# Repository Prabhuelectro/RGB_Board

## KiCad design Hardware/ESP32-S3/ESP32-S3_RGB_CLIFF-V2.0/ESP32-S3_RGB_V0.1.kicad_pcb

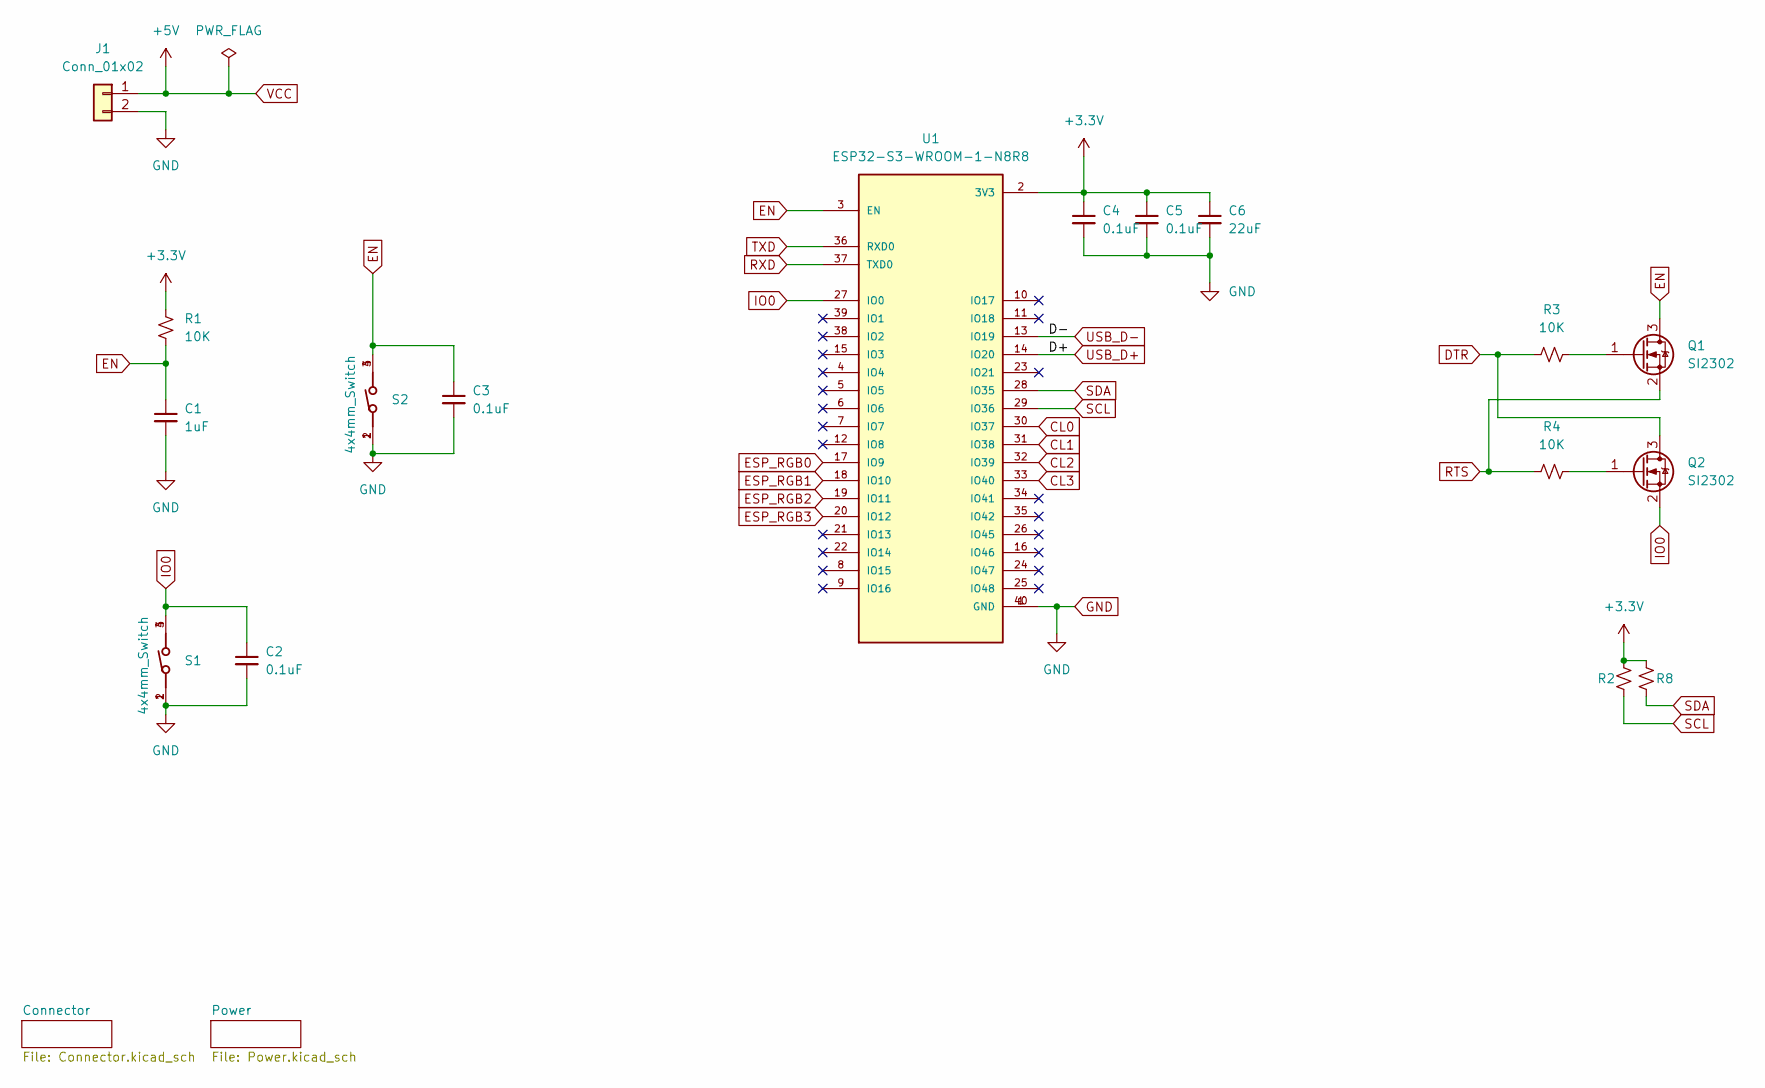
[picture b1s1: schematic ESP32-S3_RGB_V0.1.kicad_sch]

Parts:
C1: 1uF; C_0603_1608Metric
C2, C3, C4, C5: 0.1uF; C_0603_1608Metric
C6: 22uF; C_0603_1608Metric
J1: Conn_01x02; JST_VH_B2P-VH-B_1x02_P3.96mm_Vertical
Q1, Q2: SI2302; SOT-23
R1, R2, R3, R4, R8: 10K; R_0603_1608Metric
S1, S2: 4x4mm_Switch; 430181038816
U1: ESP32-S3-WROOM-1-N8R8; ESP32S3WROOM1N8R8

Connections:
+3.3V: C4.1, C5.1, C6.1, R1.1, R2.1, R8.1, U1.2 (3V3); also elsewhere on the board
CL0: U1.30 (IO37); also elsewhere on the board
CL1: U1.31 (IO38); also elsewhere on the board
CL2: U1.32 (IO39); also elsewhere on the board
CL3: U1.33 (IO40); also elsewhere on the board
DTR: Q2.3 (D), R3.2; also elsewhere on the board
EN: C1.1, C3.1, Q1.3 (D), R1.2, S2.3, S2.4, U1.3 (EN)
ESP_RGB0: U1.17 (IO9); also elsewhere on the board
ESP_RGB1: U1.18 (IO10); also elsewhere on the board
ESP_RGB2: U1.19 (IO11); also elsewhere on the board
ESP_RGB3: U1.20 (IO12); also elsewhere on the board
GND: C1.2, C2.2, C3.2, C4.2, C5.2, C6.2, J1.2, S1.1, S1.2, S2.1, S2.2, U1.1 (GND), U1.40 (GND); also elsewhere on the board
IO0: C2.1, Q2.2 (S), S1.3, S1.4, U1.27 (IO0)
unnamed: Q1.1 (G), R3.1
unnamed: Q2.1 (G), R4.1
RTS: Q1.2 (S), R4.2; also elsewhere on the board
RXD: U1.37 (TXD0); also elsewhere on the board
SCL: R2.2, U1.29 (IO36); also elsewhere on the board
SDA: R8.2, U1.28 (IO35); also elsewhere on the board
TXD: U1.36 (RXD0); also elsewhere on the board
USB_D+: U1.14 (IO20); also elsewhere on the board
USB_D-: U1.13 (IO19); also elsewhere on the board
VCC: J1.1; also elsewhere on the board

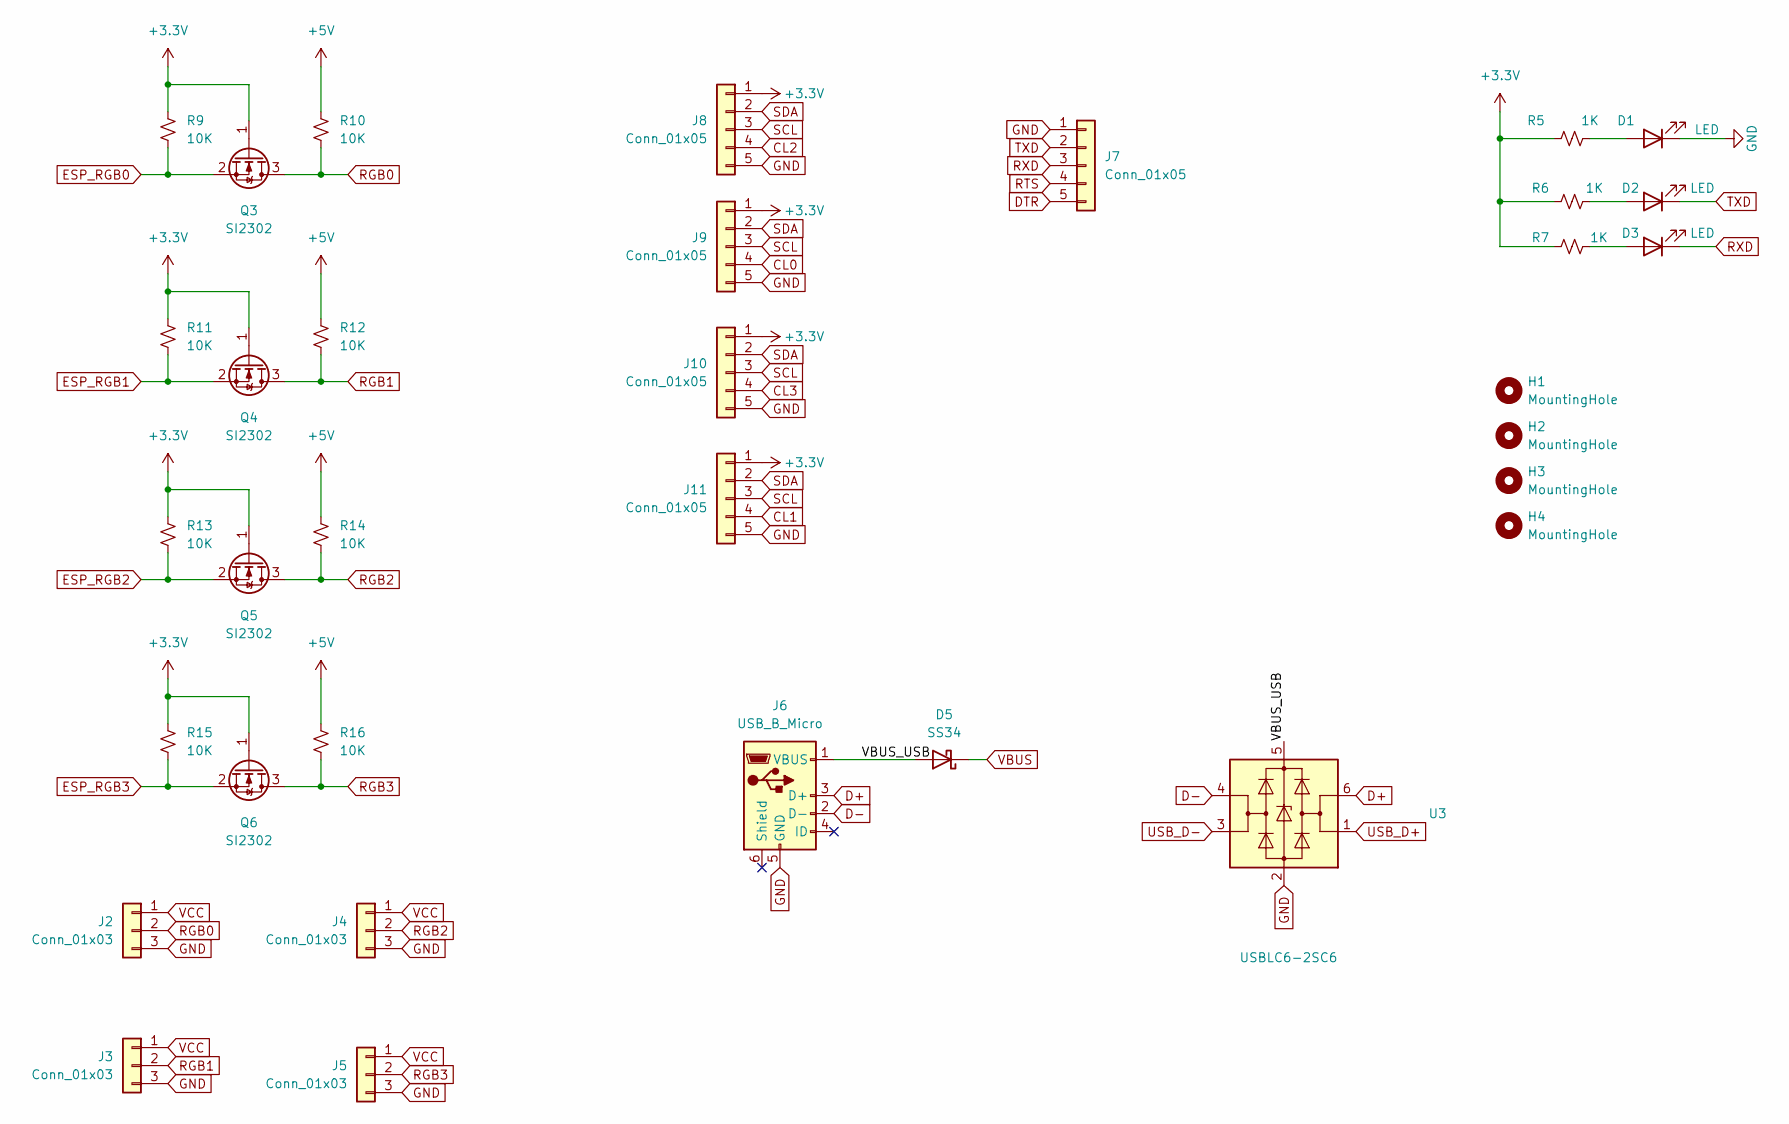
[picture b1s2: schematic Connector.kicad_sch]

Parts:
D1, D2, D3: LED; LED_0603_1608Metric
D5: SS34; D_SMA
H1, H2, H3, H4: MountingHole; MountingHole_3.2mm_M3
J2, J3, J4, J5: Conn_01x03; JST_PH_B3B-PH-K_1x03_P2.00mm_Vertical
J6: USB_B_Micro; USB_Micro-B_Wuerth_614105150721_Vertical
J7: Conn_01x05; PinHeader_1x05_P2.54mm_Vertical
J8, J9, J10, J11: Conn_01x05; JST_PH_B5B-PH-K_1x05_P2.00mm_Vertical
Q3, Q4, Q5, Q6: SI2302; SOT-23
R5, R6, R7: 1K; R_0603_1608Metric
R9, R10, R11, R12, R13, R14, R15, R16: 10K; R_0603_1608Metric
U3: USBLC6-2SC6; SOT-23-6

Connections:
+3.3V: J8.1, J9.1, J10.1, J11.1, Q3.1 (G), Q4.1 (G), Q5.1 (G), Q6.1 (G), R5.1, R6.1, R7.1, R9.1, R11.1, R13.1, R15.1; also elsewhere on the board
/Connector/VBUS_USB: D5.2 (A), J6.1 (VBUS), U3.5 (VBUS)
CL0: J9.4; also elsewhere on the board
CL1: J11.4; also elsewhere on the board
CL2: J8.4; also elsewhere on the board
CL3: J10.4; also elsewhere on the board
D+: J6.3 (D+), U3.6 (I/O1)
D-: J6.2 (D-), U3.4 (I/O2)
DTR: J7.5; also elsewhere on the board
ESP_RGB0: Q3.2 (S), R9.2; also elsewhere on the board
ESP_RGB1: Q4.2 (S), R11.2; also elsewhere on the board
ESP_RGB2: Q5.2 (S), R13.2; also elsewhere on the board
ESP_RGB3: Q6.2 (S), R15.2; also elsewhere on the board
GND: D1.1 (K), J2.3, J3.3, J4.3, J5.3, J6.5 (GND), J7.1, J8.5, J9.5, J10.5, J11.5, U3.2 (GND); also elsewhere on the board
unnamed: D1.2 (A), R5.2
unnamed: D2.2 (A), R6.2
unnamed: D3.2 (A), R7.2
RGB0: J2.2, Q3.3 (D), R10.2
RGB1: J3.2, Q4.3 (D), R12.2
RGB2: J4.2, Q5.3 (D), R14.2
RGB3: J5.2, Q6.3 (D), R16.2
RTS: J7.4; also elsewhere on the board
RXD: D3.1 (K), J7.3; also elsewhere on the board
SCL: J8.3, J9.3, J10.3, J11.3; also elsewhere on the board
SDA: J8.2, J9.2, J10.2, J11.2; also elsewhere on the board
TXD: D2.1 (K), J7.2; also elsewhere on the board
USB_D+: U3.1 (I/O1); also elsewhere on the board
USB_D-: U3.3 (I/O2); also elsewhere on the board
VBUS: D5.1 (K); also elsewhere on the board
VCC: J2.1, J3.1, J4.1, J5.1, R10.1, R12.1, R14.1, R16.1; also elsewhere on the board

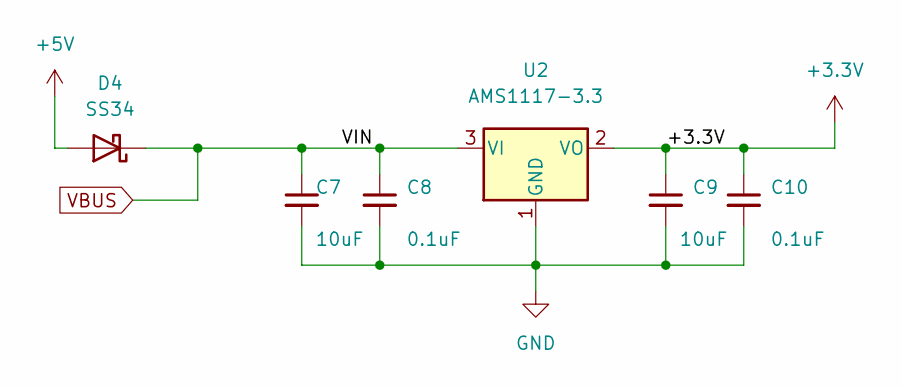
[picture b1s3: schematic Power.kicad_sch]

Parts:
C7, C9: 10uF; C_0603_1608Metric
C8, C10: 0.1uF; C_0603_1608Metric
D4: SS34; D_SMA
U2: AMS1117-3.3; SOT-223-3_TabPin2

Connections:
+3.3V: C9.1, C10.1, U2.2 (VO); also elsewhere on the board
GND: C7.2, C8.2, C9.2, C10.2, U2.1 (GND); also elsewhere on the board
VBUS: C7.1, C8.1, D4.1 (K), U2.3 (VI); also elsewhere on the board
VCC: D4.2 (A); also elsewhere on the board

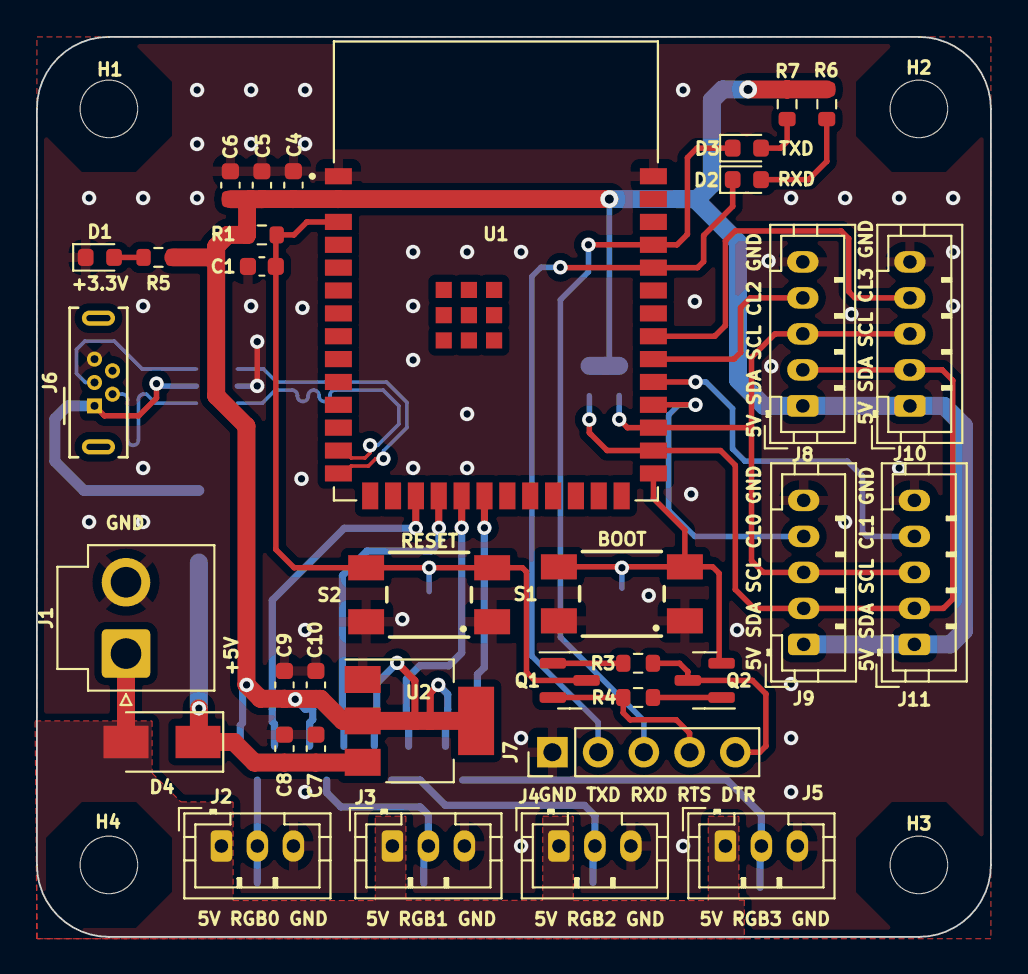
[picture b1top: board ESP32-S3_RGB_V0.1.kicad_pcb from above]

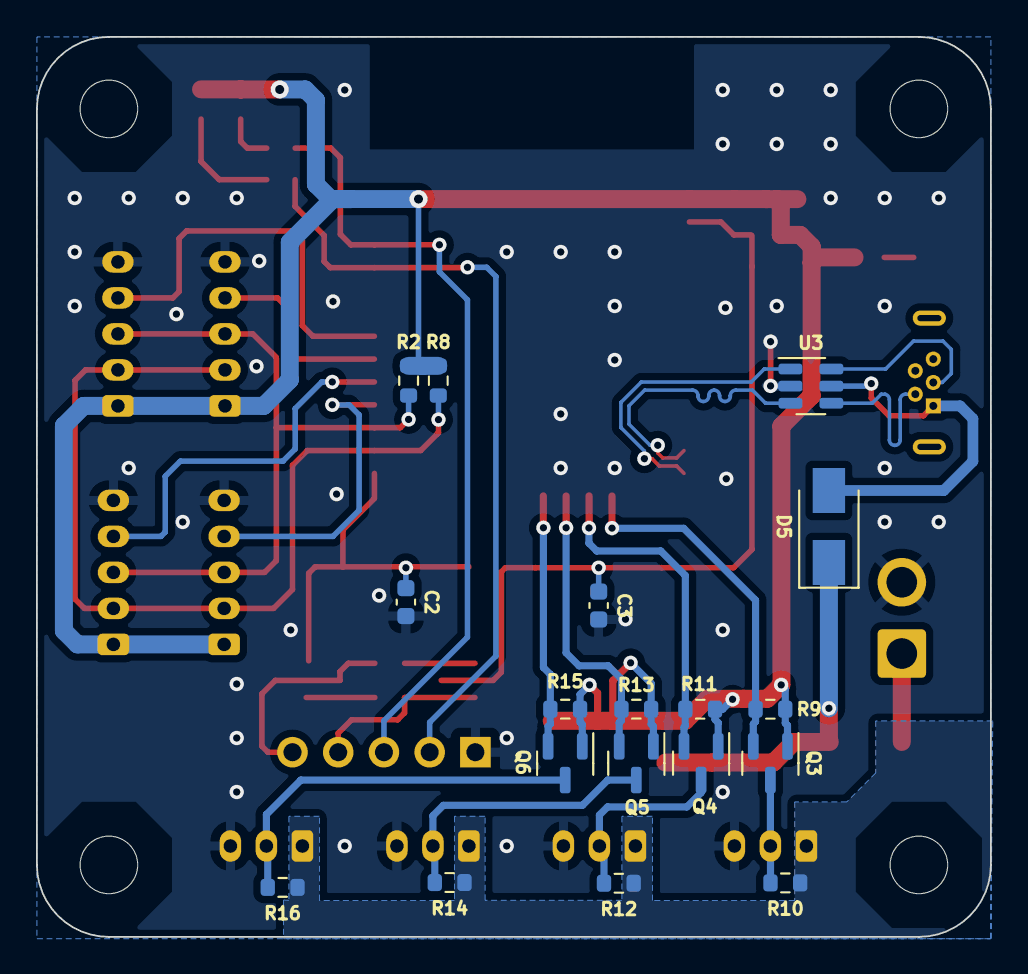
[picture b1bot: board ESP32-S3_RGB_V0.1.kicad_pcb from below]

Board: 2 copper layers, 53.0 x 50.0 mm, 57 parts (18 on the bottom side), 34 nets.

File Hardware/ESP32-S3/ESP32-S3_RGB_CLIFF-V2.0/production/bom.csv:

Designator,Footprint,Quantity,Value,LCSC Part #
C1,0603,1,1uF,
"C10, C2, C3, C4, C5, C8",0603,6,0.1uF,
C6,0603,1,22uF,
"C7, C9",0603,2,10uF,
"D1, D2, D3",0603,3,LED,
"D4, D5",D_SMA,2,SS34,
"H1, H2, H3, H4",MountingHole_3.2mm_M3,4,MountingHole,
J1,JST_VH_B2P-VH-B_1x02_P3.96mm_Vertical,1,Conn_01x02,
"J10, J11, J8, J9",JST_PH_B5B-PH-K_1x05_P2.00mm_Vertical,4,Conn_01x05,
"J2, J3, J4, J5",JST_PH_B3B-PH-K_1x03_P2.00mm_Vertical,4,Conn_01x03,
J6,USB_Micro-B_Wuerth_614105150721_Vertical,1,USB_B_Micro,
J7,PinHeader_1x05_P2.54mm_Vertical,1,Conn_01x05,
"Q1, Q2, Q3, Q4, Q5, Q6",SOT-23,6,SI2302,
"R1, R10, R11, R12, R13, R14, R15, R16, R2, R3, R4, R8, R9",0603,13,10K,
"R5, R6, R7",0603,3,1K,
"S1, S2",430181038816,2,4x4mm_Switch,
U1,ESP32S3WROOM1N8R8,1,ESP32-S3-WROOM-1-N8R8,
U2,SOT-223-3_TabPin2,1,AMS1117-3.3,
U3,SOT-23-6,1,USBLC6-2SC6,

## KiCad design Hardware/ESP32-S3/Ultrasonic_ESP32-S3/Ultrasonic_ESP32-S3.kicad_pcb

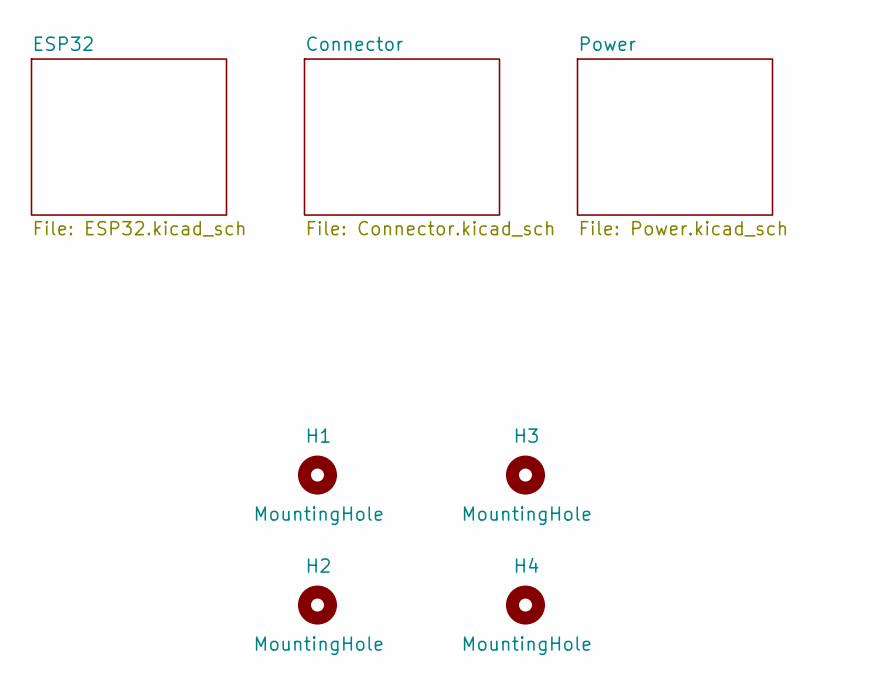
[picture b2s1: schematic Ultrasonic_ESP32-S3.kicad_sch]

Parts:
H1, H2, H3, H4: MountingHole; MountingHole_3.2mm_M3

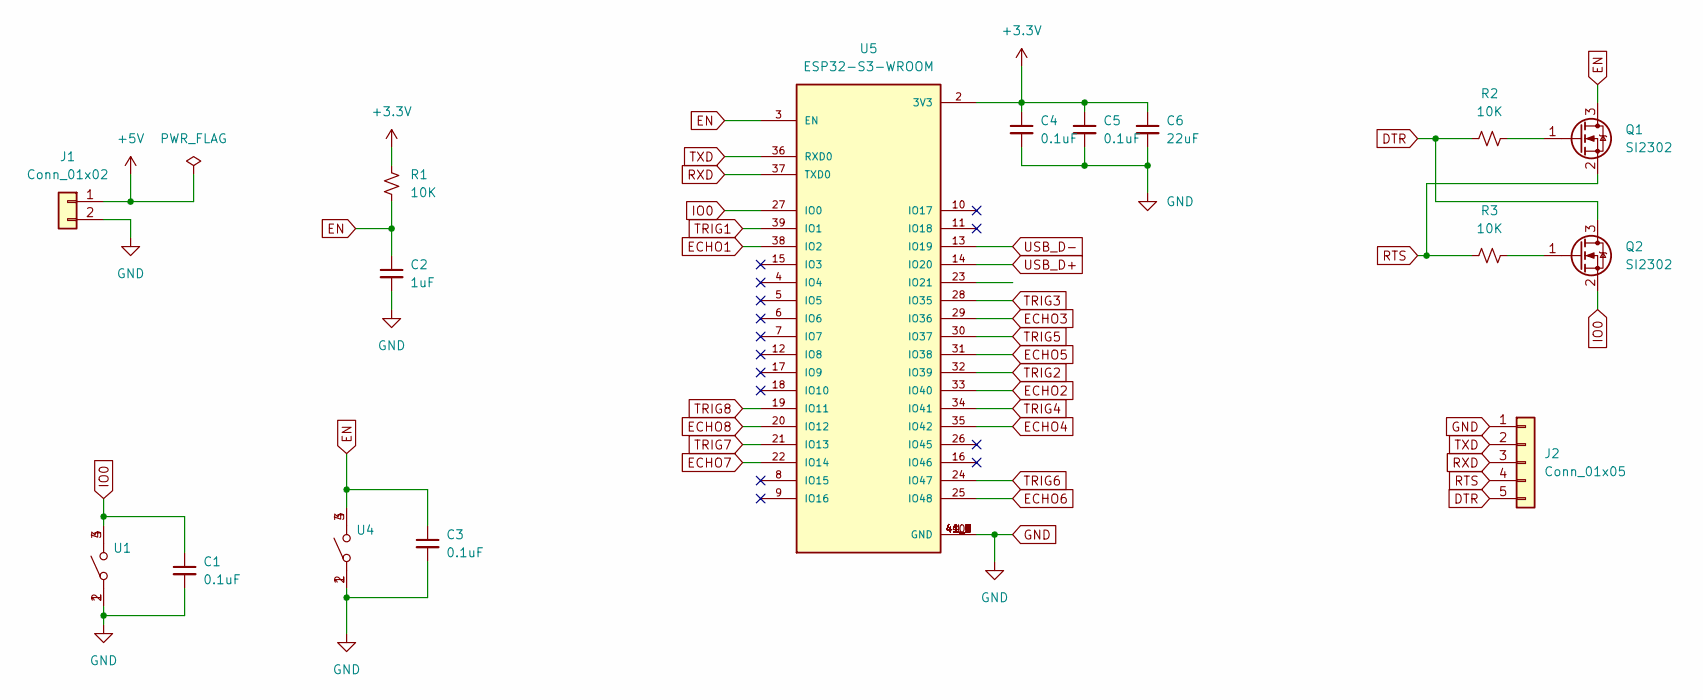
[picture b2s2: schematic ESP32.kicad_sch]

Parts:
C1, C3, C4, C5: 0.1uF; C_0603_1608Metric
C2: 1uF; C_0603_1608Metric
C6: 22uF; C_0603_1608Metric
J1: Conn_01x02; JST_VH_B2P-VH-B_1x02_P3.96mm_Vertical
J2: Conn_01x05; PinHeader_1x05_P2.54mm_Vertical
Q1, Q2: SI2302; SOT-23
R1, R2, R3: 10K; R_0603_1608Metric
U1, U4: Tactile_Switch
U5: ESP32-S3-WROOM; ESP32-S3-WROOM1-N4R2

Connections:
+3.3V: C4.1, C5.1, C6.1, R1.1, U5.2 (3V3); also elsewhere on the board
+5V: J1.1; also elsewhere on the board
DTR: J2.5, Q2.3 (D), R2.2
ECHO1: U5.38 (IO2); also elsewhere on the board
ECHO2: U5.33 (IO40); also elsewhere on the board
ECHO3: U5.29 (IO36); also elsewhere on the board
ECHO4: U5.35 (IO42); also elsewhere on the board
ECHO5: U5.31 (IO38); also elsewhere on the board
ECHO6: U5.25 (IO48); also elsewhere on the board
ECHO7: U5.22 (IO14); also elsewhere on the board
ECHO8: U5.20 (IO12); also elsewhere on the board
EN: C2.1, C3.1, Q1.3 (D), R1.2, U4.3, U4.4, U5.3 (EN)
GND: C1.2, C2.2, C3.2, C4.2, C5.2, C6.2, J1.2, J2.1, U1.1, U1.2, U4.1, U4.2, U5.1 (GND), U5.40 (GND), U5.41_1 (GND), U5.41_2 (GND), U5.41_3 (GND), U5.41_4 (GND), U5.41_5 (GND), U5.41_6 (GND), U5.41_7 (GND), U5.41_8 (GND), U5.41_9 (GND); also elsewhere on the board
IO0: C1.1, Q2.2 (S), U1.3, U1.4, U5.27 (IO0)
unnamed: Q1.1 (G), R2.1
unnamed: Q2.1 (G), R3.1
RTS: J2.4, Q1.2 (S), R3.2
RXD: J2.3, U5.37 (TXD0); also elsewhere on the board
TRIG1: U5.39 (IO1); also elsewhere on the board
TRIG2: U5.32 (IO39); also elsewhere on the board
TRIG3: U5.28 (IO35); also elsewhere on the board
TRIG4: U5.34 (IO41); also elsewhere on the board
TRIG5: U5.30 (IO37); also elsewhere on the board
TRIG6: U5.24 (IO47); also elsewhere on the board
TRIG7: U5.21 (IO13); also elsewhere on the board
TRIG8: U5.19 (IO11); also elsewhere on the board
TXD: J2.2, U5.36 (RXD0); also elsewhere on the board
USB_D+: U5.14 (IO20); also elsewhere on the board
USB_D-: U5.13 (IO19); also elsewhere on the board

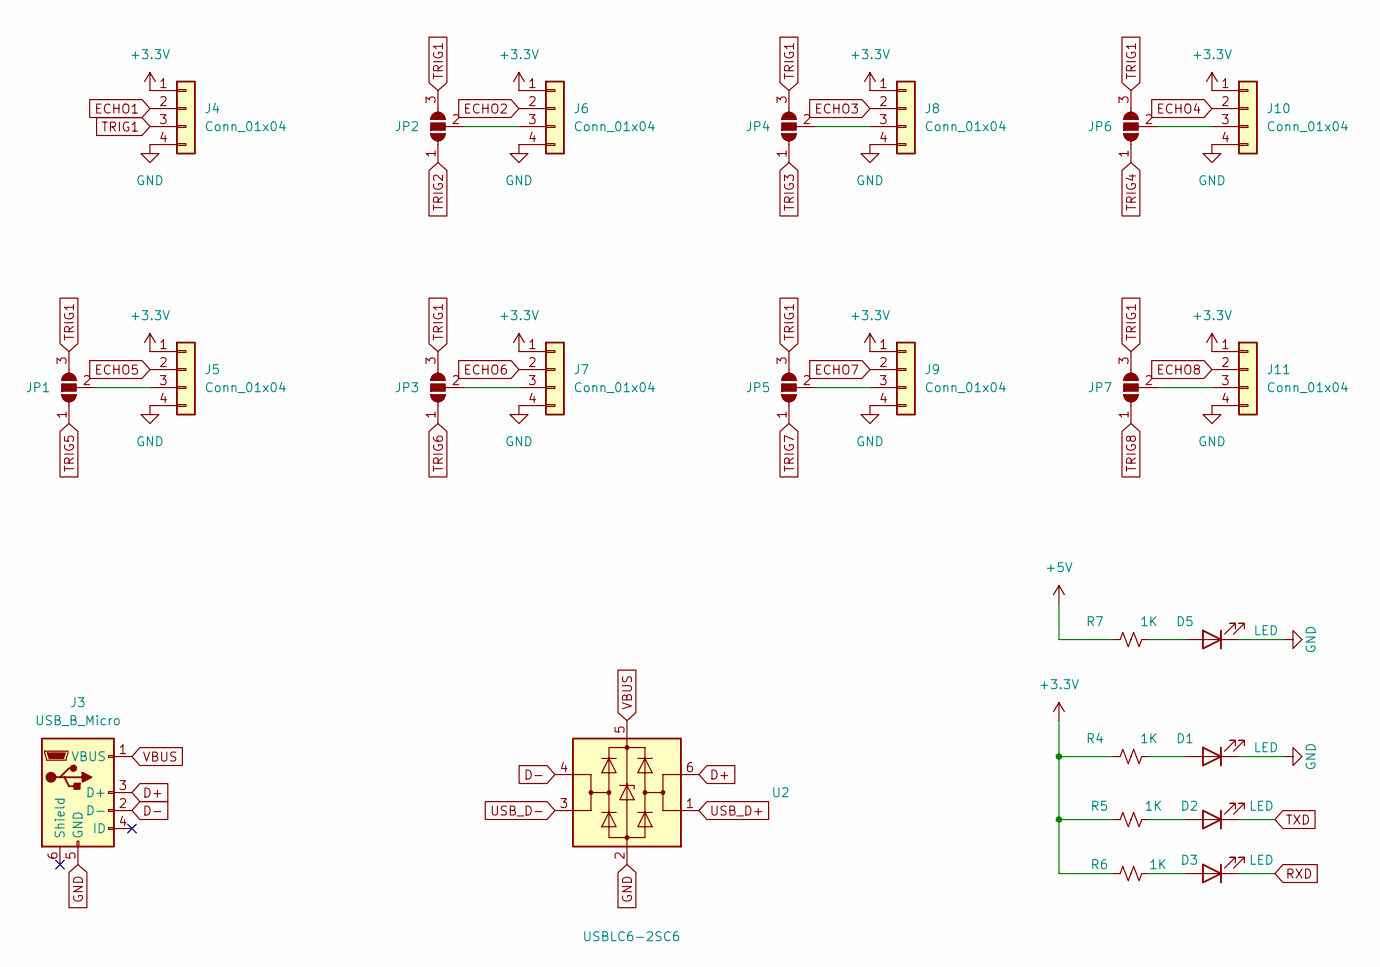
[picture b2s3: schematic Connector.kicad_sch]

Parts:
D1, D2, D3, D5: LED; LED_0603_1608Metric
J3: USB_B_Micro; USB_Micro-B_Wuerth_614105150721_Vertical
J4, J5, J6, J7, J8, J9, J10, J11: Conn_01x04; JST_PH_B4B-PH-K_1x04_P2.00mm_Vertical
JP1, JP2, JP3, JP4, JP5, JP6, JP7: SolderJumper_3_Open; SolderJumper-3_P1.3mm_Open_Pad1.0x1.5mm
R4, R5, R6, R7: 1K; R_0603_1608Metric
U2: USBLC6-2SC6; SOT-23-6

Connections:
+3.3V: J4.1, J5.1, J6.1, J7.1, J8.1, J9.1, J10.1, J11.1, R4.1, R5.1, R6.1; also elsewhere on the board
+5V: R7.1; also elsewhere on the board
D+: J3.3 (D+), U2.6 (I/O1)
D-: J3.2 (D-), U2.4 (I/O2)
ECHO1: J4.2; also elsewhere on the board
ECHO2: J6.2; also elsewhere on the board
ECHO3: J8.2; also elsewhere on the board
ECHO4: J10.2; also elsewhere on the board
ECHO5: J5.2; also elsewhere on the board
ECHO6: J7.2; also elsewhere on the board
ECHO7: J9.2; also elsewhere on the board
ECHO8: J11.2; also elsewhere on the board
GND: D1.1 (K), D5.1 (K), J3.5 (GND), J4.4, J5.4, J6.4, J7.4, J8.4, J9.4, J10.4, J11.4, U2.2 (GND); also elsewhere on the board
unnamed: D1.2 (A), R4.2
unnamed: D2.2 (A), R5.2
unnamed: D3.2 (A), R6.2
unnamed: D5.2 (A), R7.2
unnamed: J5.3, JP1.2 (C)
unnamed: J6.3, JP2.2 (C)
unnamed: J7.3, JP3.2 (C)
unnamed: J8.3, JP4.2 (C)
unnamed: J9.3, JP5.2 (C)
unnamed: J10.3, JP6.2 (C)
unnamed: J11.3, JP7.2 (C)
RXD: D3.1 (K); also elsewhere on the board
TRIG1: J4.3, JP1.3 (B), JP2.3 (B), JP3.3 (B), JP4.3 (B), JP5.3 (B), JP6.3 (B), JP7.3 (B); also elsewhere on the board
TRIG2: JP2.1 (A); also elsewhere on the board
TRIG3: JP4.1 (A); also elsewhere on the board
TRIG4: JP6.1 (A); also elsewhere on the board
TRIG5: JP1.1 (A); also elsewhere on the board
TRIG6: JP3.1 (A); also elsewhere on the board
TRIG7: JP5.1 (A); also elsewhere on the board
TRIG8: JP7.1 (A); also elsewhere on the board
TXD: D2.1 (K); also elsewhere on the board
USB_D+: U2.1 (I/O1); also elsewhere on the board
USB_D-: U2.3 (I/O2); also elsewhere on the board
VBUS: J3.1 (VBUS), U2.5 (VBUS)

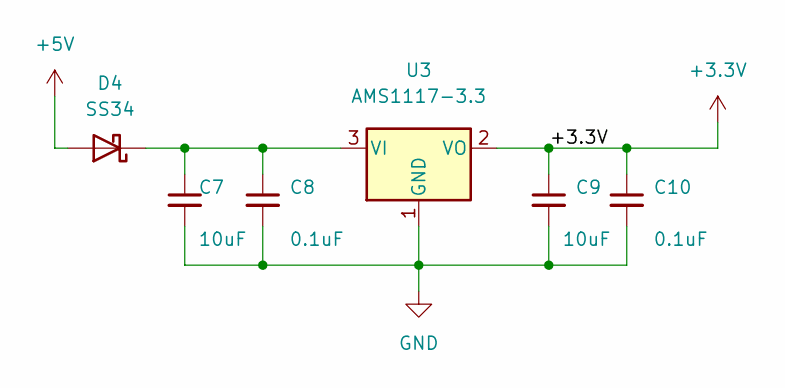
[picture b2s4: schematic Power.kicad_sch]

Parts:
C7, C9: 10uF; C_0603_1608Metric
C8, C10: 0.1uF; C_0603_1608Metric
D4: SS34; D_SMA
U3: AMS1117-3.3; SOT-223-3_TabPin2

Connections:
+3.3V: C9.1, C10.1, U3.2 (VO); also elsewhere on the board
+5V: D4.2 (A); also elsewhere on the board
GND: C7.2, C8.2, C9.2, C10.2, U3.1 (GND); also elsewhere on the board
unnamed: C7.1, C8.1, D4.1 (K), U3.3 (VI)

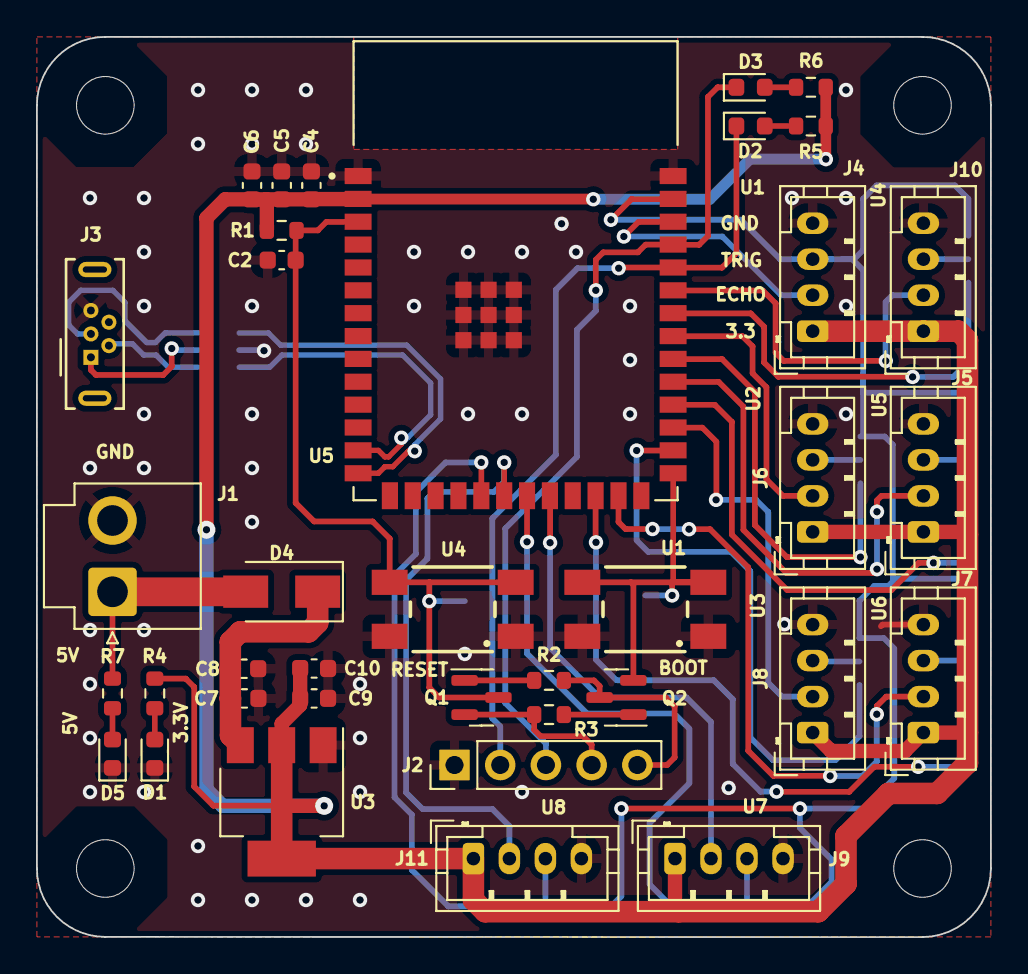
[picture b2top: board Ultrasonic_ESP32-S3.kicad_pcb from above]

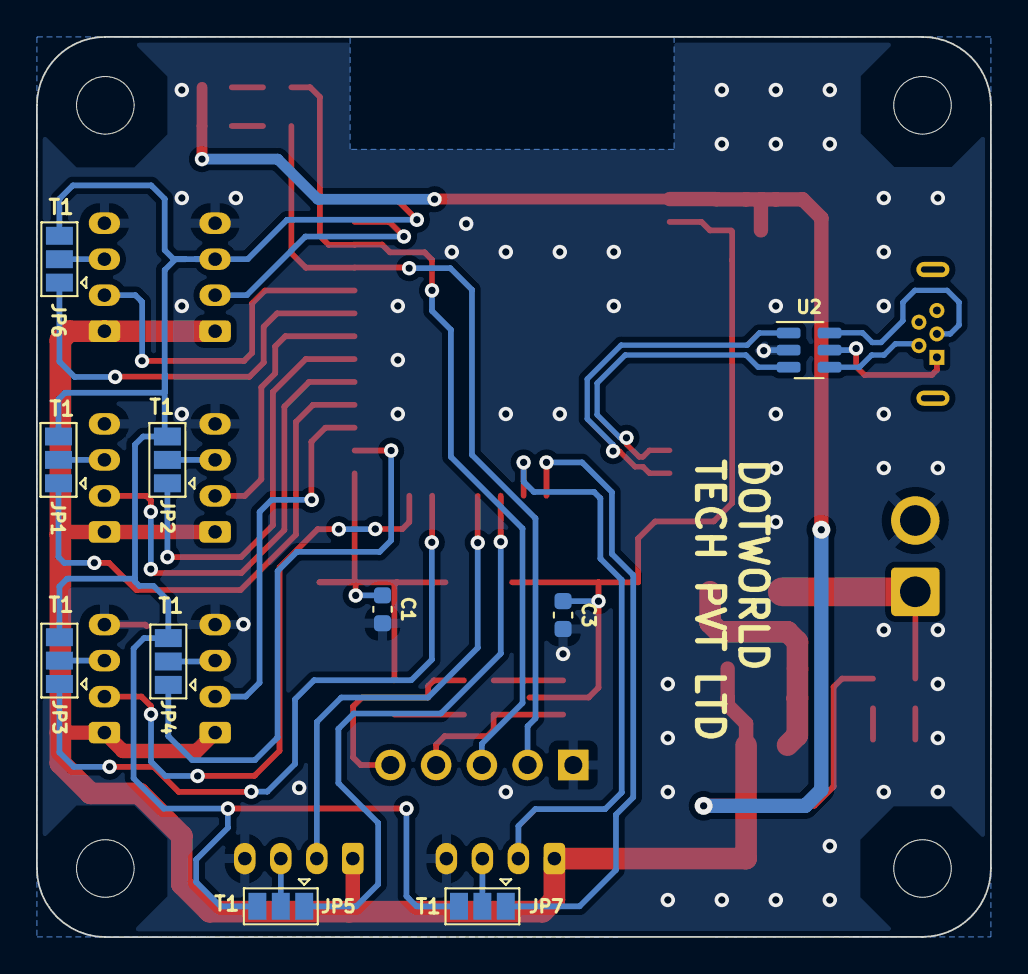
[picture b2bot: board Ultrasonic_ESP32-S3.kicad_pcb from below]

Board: 2 copper layers, 53.0 x 50.0 mm, 51 parts (10 on the bottom side), 44 nets.

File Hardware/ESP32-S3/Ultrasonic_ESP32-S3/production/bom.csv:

Designator,Footprint,Quantity,Value,LCSC Part #
"C1, C10, C3, C4, C5, C8",0603,6,0.1uF,
C2,0603,1,1uF,
C6,0603,1,22uF,
"C7, C9",0603,2,10uF,
"D1, D2, D3, D5",0603,4,LED,
D4,D_SMA,1,SS34,
"H1, H2, H3, H4",MountingHole_3.2mm_M3,4,MountingHole,
J1,JST_VH_B2P-VH-B_1x02_P3.96mm_Vertical,1,Conn_01x02,
"J10, J11, J4, J5, J6, J7, J8, J9",JST_PH_B4B-PH-K_1x04_P2.00mm_Vertical,8,Conn_01x04,
J2,PinHeader_1x05_P2.54mm_Vertical,1,Conn_01x05,
J3,USB_Micro-B_Wuerth_614105150721_Vertical,1,USB_B_Micro,
"JP1, JP2, JP3, JP4, JP5, JP6, JP7",SolderJumper-3_P1.3mm_Open_Pad1.0x1.5mm,7,SolderJumper_3_Open,
"Q1, Q2",SOT-23,2,SI2302,
"R1, R2, R3",0603,3,10K,
"R4, R5, R6, R7",0603,4,1K,
"U1, U4",Tactile_Switch,2,Tactile_Switch,
U2,SOT-23-6,1,USBLC6-2SC6,
U3,SOT-223-3_TabPin2,1,AMS1117-3.3,
U5,ESP32-S3-WROOM1-N4R2,1,ESP32-S3-WROOM,

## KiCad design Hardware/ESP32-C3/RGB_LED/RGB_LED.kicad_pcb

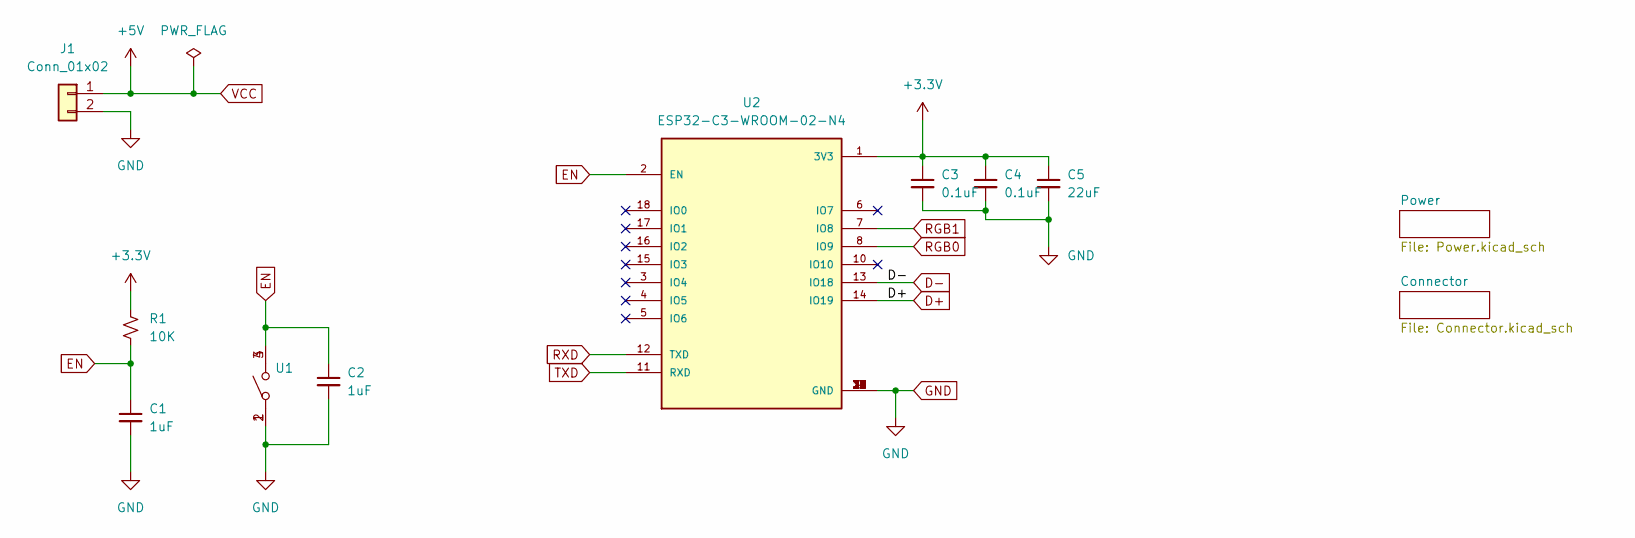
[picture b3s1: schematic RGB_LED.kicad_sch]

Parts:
C1, C2: 1uF; C_0603_1608Metric
C3, C4: 0.1uF; C_0603_1608Metric
C5: 22uF; C_0603_1608Metric
J1: Conn_01x02; JST_VH_B2P-VH-B_1x02_P3.96mm_Vertical
R1: 10K; R_0603_1608Metric
U1: Tactile_Switch
U2: ESP32-C3-WROOM-02-N4; ESP32-C3-WROOM-02-H4

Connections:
+3.3V: C3.1, C4.1, C5.1, R1.1, U2.1 (3V3); also elsewhere on the board
D+: U2.14 (IO19); also elsewhere on the board
D-: U2.13 (IO18); also elsewhere on the board
EN: C1.1, C2.1, R1.2, U1.3, U1.4, U2.2 (EN)
GND: C1.2, C2.2, C3.2, C4.2, C5.2, J1.2, U1.1, U1.2, U2.9 (GND), U2.19 (GND), U2.20 (GND), U2.21 (GND), U2.22 (GND), U2.23 (GND), U2.24 (GND), U2.25 (GND), U2.26 (GND), U2.27 (GND), U2.28 (GND), U2.29 (GND), U2.30 (GND), U2.31 (GND), U2.32 (GND), U2.33 (GND), U2.34 (GND), U2.35 (GND), U2.36 (GND), U2.37 (GND), U2.38 (GND), U2.39 (GND); also elsewhere on the board
RGB0: U2.8 (IO9); also elsewhere on the board
RGB1: U2.7 (IO8); also elsewhere on the board
RXD: U2.12 (TXD); also elsewhere on the board
TXD: U2.11 (RXD); also elsewhere on the board
VCC: J1.1; also elsewhere on the board

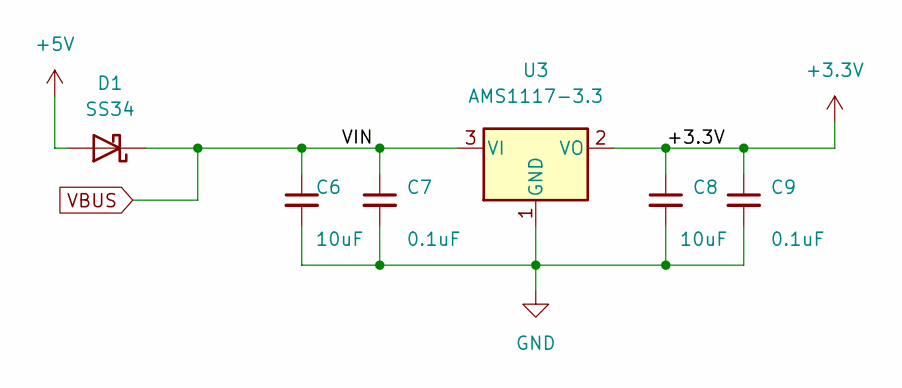
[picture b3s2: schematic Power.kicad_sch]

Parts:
C6, C8: 10uF; C_0603_1608Metric
C7, C9: 0.1uF; C_0603_1608Metric
D1: SS34; D_SMA
U3: AMS1117-3.3; SOT-223-3_TabPin2

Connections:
+3.3V: C8.1, C9.1, U3.2 (VO); also elsewhere on the board
GND: C6.2, C7.2, C8.2, C9.2, U3.1 (GND); also elsewhere on the board
VBUS: C6.1, C7.1, D1.1 (K), U3.3 (VI); also elsewhere on the board
VCC: D1.2 (A); also elsewhere on the board

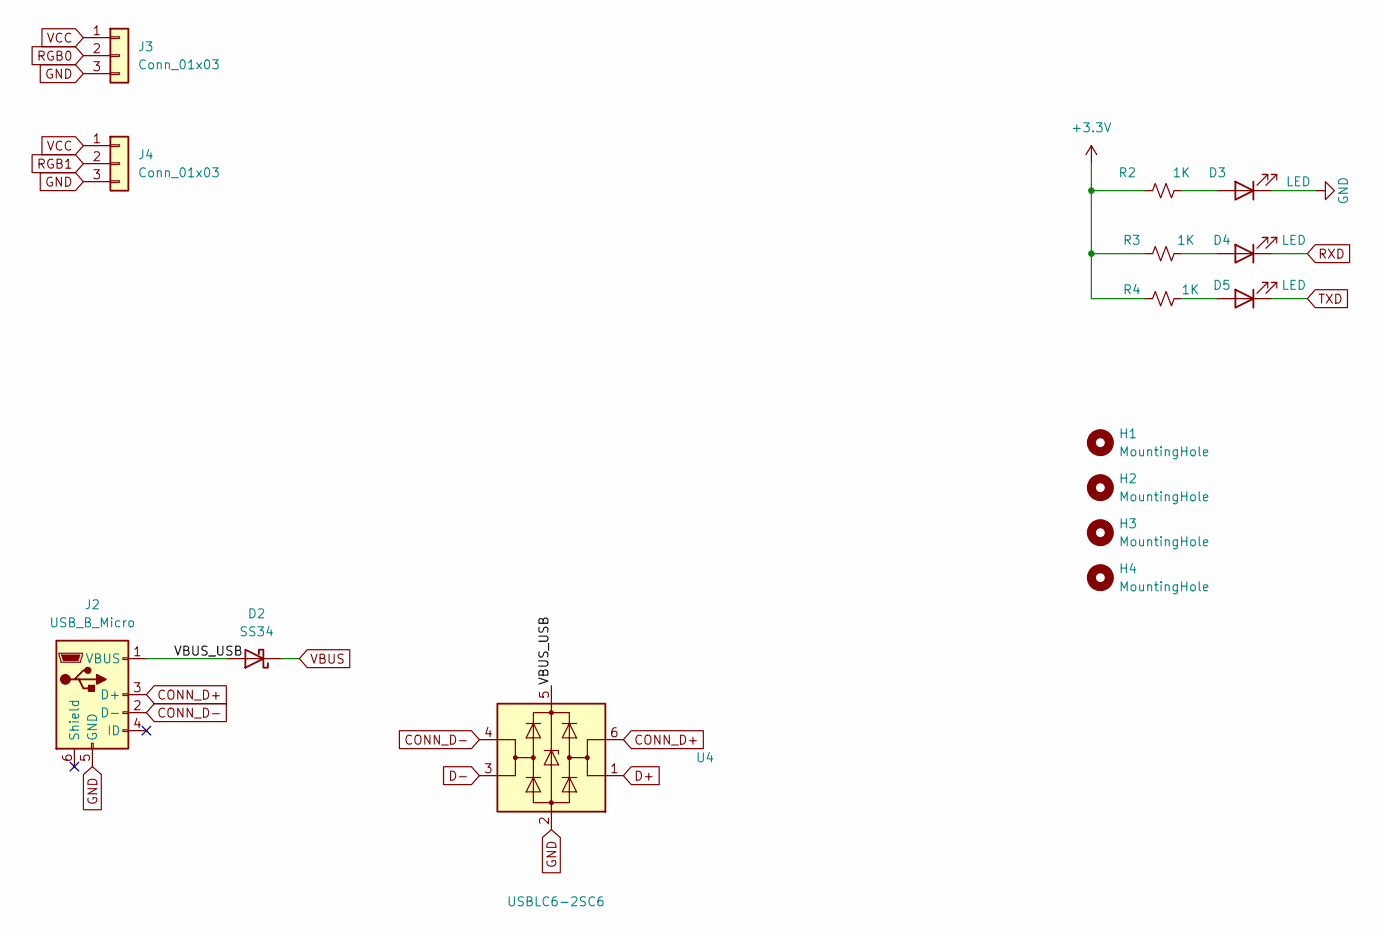
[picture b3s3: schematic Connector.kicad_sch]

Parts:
D2: SS34; D_SMA
D3, D4, D5: LED; LED_0603_1608Metric
H1, H2, H3, H4: MountingHole; MountingHole_3mm
J2: USB_B_Micro; USB_Micro-B_Wuerth_614105150721_Vertical
J3, J4: Conn_01x03; JST_PH_B3B-PH-K_1x03_P2.00mm_Vertical
R2, R3, R4: 1K; R_0603_1608Metric
U4: USBLC6-2SC6; SOT-23-6

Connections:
+3.3V: R2.1, R3.1, R4.1; also elsewhere on the board
/Connector/VBUS_USB: D2.2 (A), J2.1 (VBUS), U4.5 (VBUS)
CONN_D+: J2.3 (D+), U4.6 (I/O1)
CONN_D-: J2.2 (D-), U4.4 (I/O2)
D+: U4.1 (I/O1); also elsewhere on the board
D-: U4.3 (I/O2); also elsewhere on the board
GND: D3.1 (K), J2.5 (GND), J3.3, J4.3, U4.2 (GND); also elsewhere on the board
unnamed: D3.2 (A), R2.2
unnamed: D4.2 (A), R3.2
unnamed: D5.2 (A), R4.2
RGB0: J3.2; also elsewhere on the board
RGB1: J4.2; also elsewhere on the board
RXD: D4.1 (K); also elsewhere on the board
TXD: D5.1 (K); also elsewhere on the board
VBUS: D2.1 (K); also elsewhere on the board
VCC: J3.1, J4.1; also elsewhere on the board
